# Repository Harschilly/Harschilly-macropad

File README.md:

# Harschilly-macropad
My Macropad For Hack club(Hack pad)

# BOM
9x MX style switches

1x SEEEDUINO XIAO RP2040

9x Through-hole 1N4148 diodes

1x SSD1306 128x32 OLED 0.91"

9x Blank DSA Keycaps

1x ec11 rotary encoder

1x 1x4 2.54mm female header

1x 3d printed case(own)

1x 3d printed knop (own)

# Assembled MacroPad

# My Schematic

# My PCB

# 3d Viewer PCB

# Case 

Design inspo from:cubit010

Hope you enjoy😁

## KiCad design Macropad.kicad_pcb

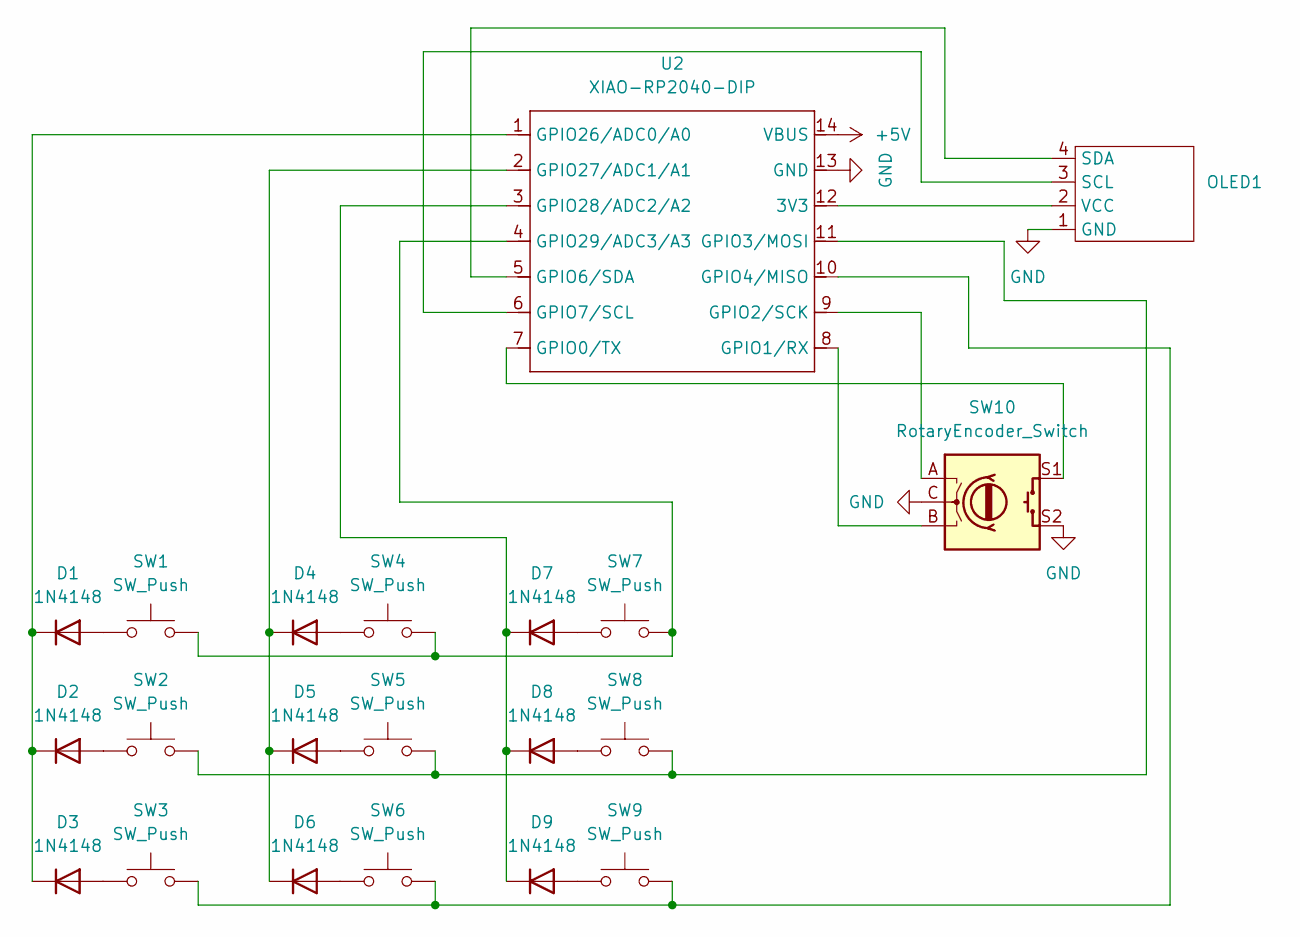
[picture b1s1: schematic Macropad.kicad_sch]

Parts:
D1, D2, D3, D4, D5, D6, D7, D8, D9: 1N4148; D_DO-35_SOD27_P7.62mm_Horizontal
OLED1: OLED_0.91_128x32
SW1, SW2, SW3, SW4, SW5, SW6, SW7, SW8, SW9: SW_Push; SW_Cherry_MX_1.00u_PCB
SW10: RotaryEncoder_Switch; RotaryEncoder_Alps_EC11E-Switch_Vertical_H20mm
U2: XIAO-RP2040-DIP

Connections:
+5V: U2.14 (VBUS)
GND: OLED1.1 (GND), SW10.C, SW10.S2, U2.13 (GND)
unnamed: D1.2 (A), SW1.1
unnamed: D1.1 (K), D2.1 (K), D3.1 (K), U2.1 (GPIO26/ADC0/A0)
unnamed: D2.2 (A), SW2.1
unnamed: D3.2 (A), SW3.1
unnamed: D4.2 (A), SW4.1
unnamed: D4.1 (K), D5.1 (K), D6.1 (K), U2.2 (GPIO27/ADC1/A1)
unnamed: D5.2 (A), SW5.1
unnamed: D6.2 (A), SW6.1
unnamed: D7.2 (A), SW7.1
unnamed: D7.1 (K), D8.1 (K), D9.1 (K), U2.3 (GPIO28/ADC2/A2)
unnamed: D8.2 (A), SW8.1
unnamed: D9.2 (A), SW9.1
unnamed: OLED1.3 (SCL), U2.6 (GPIO7/SCL)
unnamed: OLED1.4 (SDA), U2.5 (GPIO6/SDA)
unnamed: OLED1.2 (VCC), U2.12 (3V3)
unnamed: SW10.S1, U2.7 (GPIO0/TX)
unnamed: SW10.B, U2.8 (GPIO1/RX)
unnamed: SW10.A, U2.9 (GPIO2/SCK)
unnamed: SW2.2, SW5.2, SW8.2, U2.11 (GPIO3/MOSI)
unnamed: SW3.2, SW6.2, SW9.2, U2.10 (GPIO4/MISO)
unnamed: SW1.2, SW4.2, SW7.2, U2.4 (GPIO29/ADC3/A3)

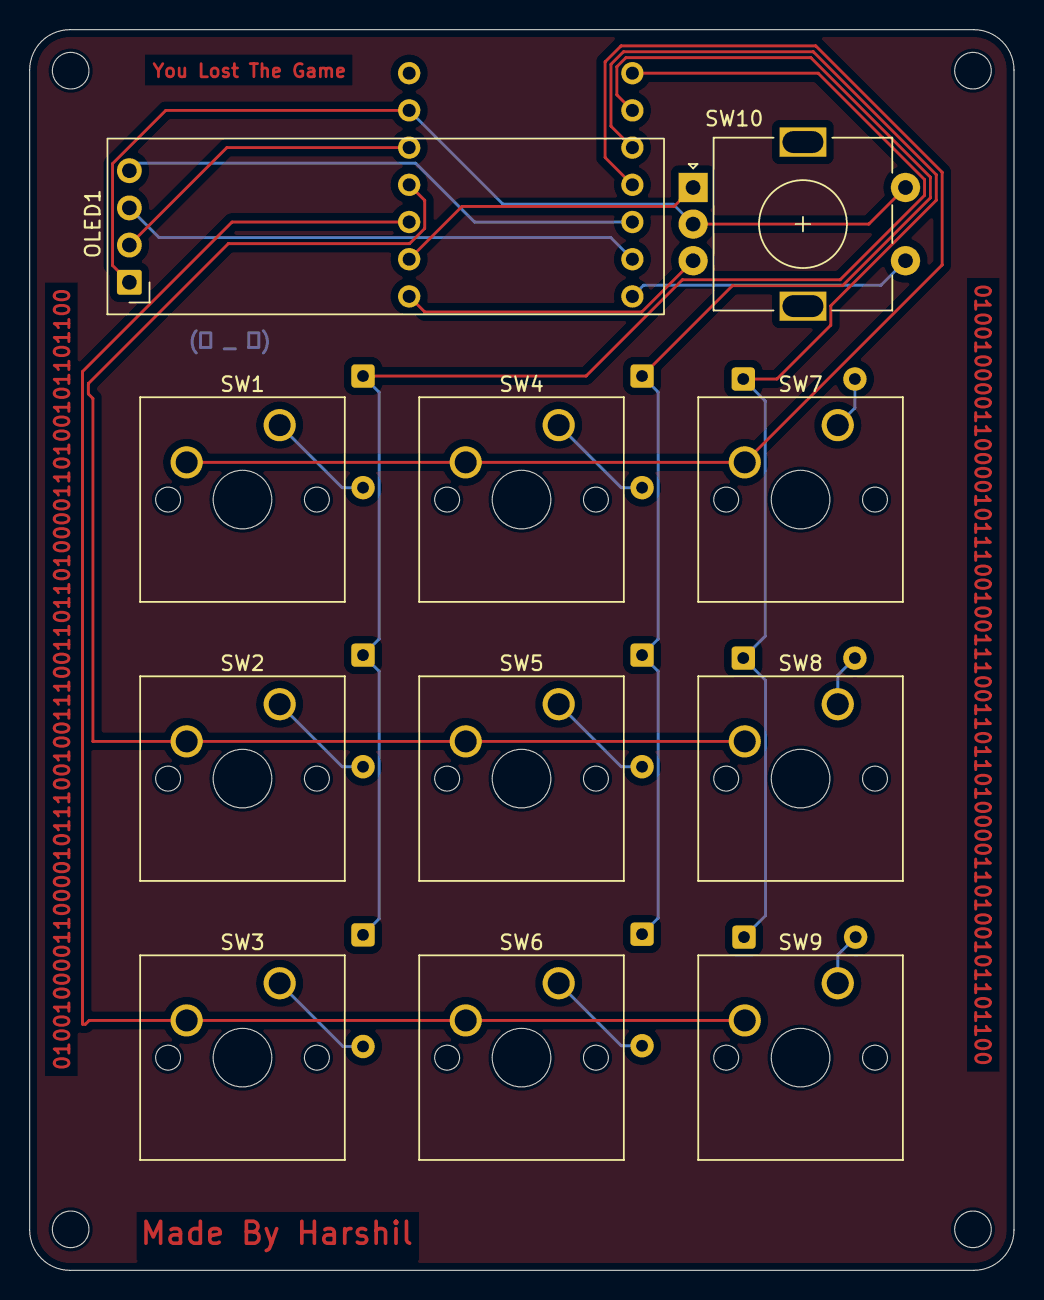
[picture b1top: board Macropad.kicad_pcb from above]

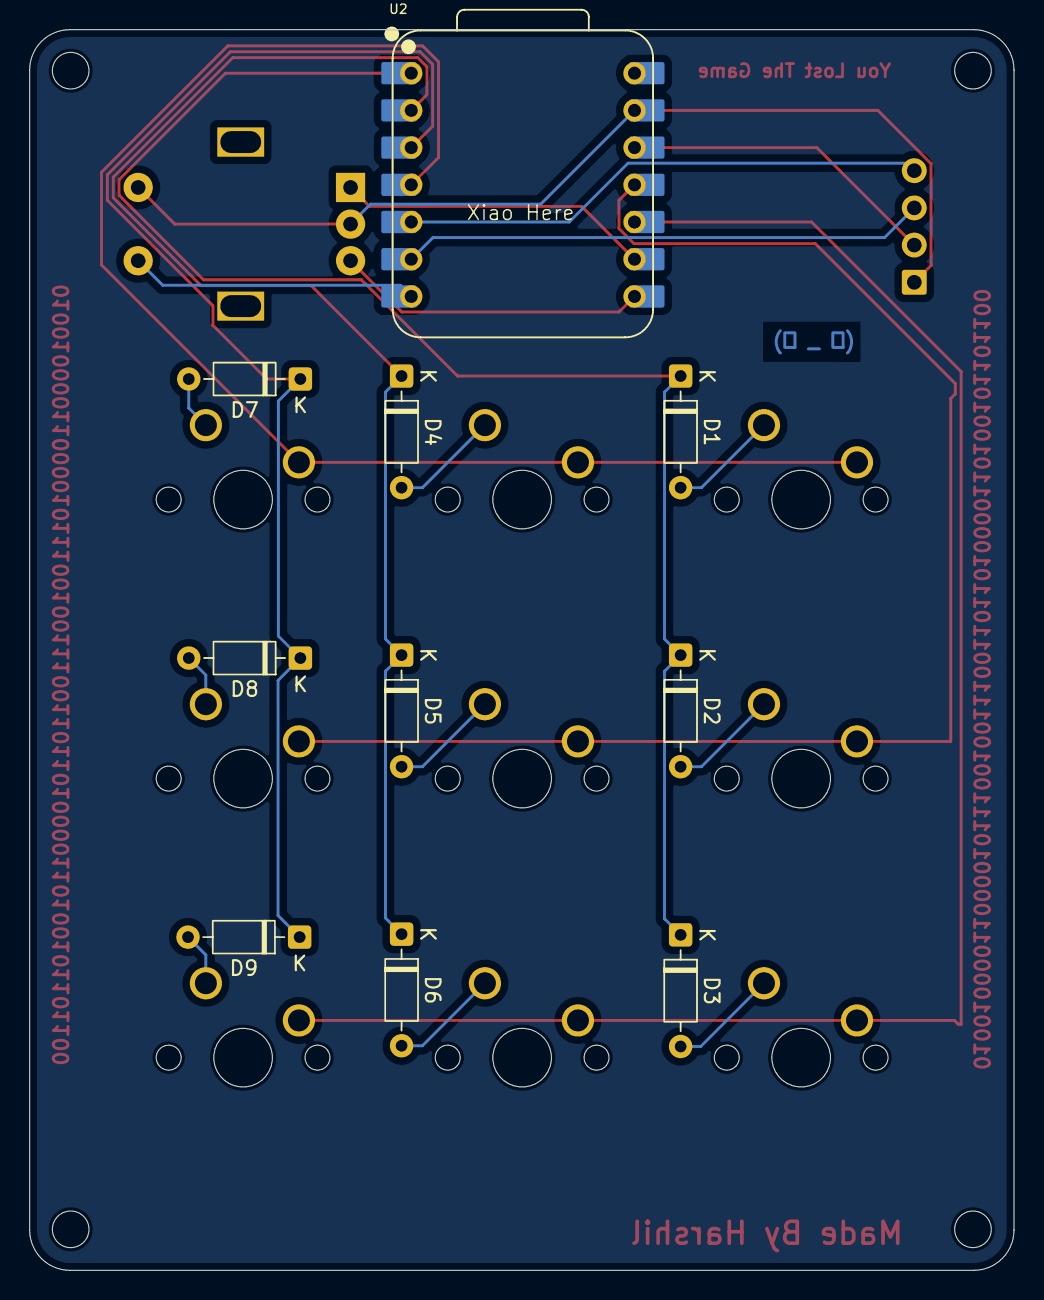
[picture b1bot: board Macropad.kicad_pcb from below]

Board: 2 copper layers, 67.2 x 84.7 mm, 21 parts (10 on the bottom side), 22 nets.

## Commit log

2026-01-15 Create PCB
2026-01-15 Create Items
